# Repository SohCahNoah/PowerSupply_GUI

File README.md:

Junior Design 2 - Project
Group: EJ16
Project: DC-to-DC Power Supply with GUI interface

Steps to operate:
1. Connect the Arduino Uno to the host computer
2. Upload the firmware to the Arduino
3. Ensure that the correct pins are connected to the system for I2C communication (SDK, SDA, 5V VCC, GND)
4. Close any active Serial communications with the Arduino (such as in the Arduino IDE)
5. Run the Python Code

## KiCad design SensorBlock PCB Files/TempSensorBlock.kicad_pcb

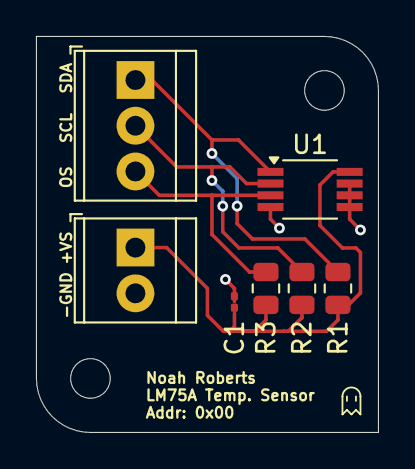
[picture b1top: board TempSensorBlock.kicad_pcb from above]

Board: 2 copper layers, 19.0 x 22.0 mm, 9 parts (0 on the bottom side), 5 nets.

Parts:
C1: 100nF; C_0201_0603Metric
H1, H1#2: MountingHole; MountingHole_2.2mm_M2
J1: Source Input (Screw); TerminalBlock_TE_282834-2_1x02_P2.54mm_Horizontal
J2: Microcontroller Terminal (Screw); TerminalBlock_TE_282834-3_1x03_P2.54mm_Horizontal
R1, R2, R3: 10k; R_0805_2012Metric
U1: LM75B; VSSOP-8_3.0x3.0mm_P0.65mm

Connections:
/+VS: C1.1, J1.1, R1.1, R2.1, R3.1, U1.8 (+Vs)
/OS: J2.3, R3.2, U1.3 (O.S.)
/SCL: J2.2, R2.2, U1.2 (SCL)
/SDA: J2.1, R1.2, U1.1 (SDA)
GND: C1.2, J1.2, U1.4 (GND), U1.5 (A2), U1.6 (A1), U1.7 (A0)

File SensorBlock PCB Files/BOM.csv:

"Reference","Value","Datasheet","Footprint","Qty","DNP","Supplier"
"H1,H2,H3,H4","MountingHole","~","MountingHole:MountingHole_2.2mm_M2","4","","(N/A)"
"R1,R2,R3","10k","~","Resistor_SMD:R_0805_2012Metric","3","","https://eecs.engineering.oregonstate.edu/education/tekbotSui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"
"C1","100nF","~","Capacitor_SMD:C_0201_0603Metric","1","","https://eecs.engineering.oregonstate.edu/education/tekbotSui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"
"U1","LM75B","http://www.ti.com/lit/ds/symlink/lm75b.pdf","Package_SO:VSSOP-8_3.0x3.0mm_P0.65mm","1","","https://eecs.engineering.oregonstate.edu/education/tekbotSui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"
"J1","Source Input (Screw)","~","TerminalBlock_TE-Connectivity:TerminalBlock_TE_282834-2_1x02_P2.54mm_Horizontal","1","","https://www.digikey.com/en/products/detail/te-connectivity-a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"
"J2","Microcontroller Terminal (Screw)","~","TerminalBlock_TE-Connectivity:TerminalBlock_TE_282834-3_1x03_P2.54mm_Horizontal","1","","https://www.digikey.com/en/products/detail/te-connectivity-a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"

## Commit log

2024-05-08 Version 1 of GUI
2024-05-08 Created EXE to run program
2024-05-08 Added Icon File
2024-05-08 Adjusted Icon Code to handle errors
2024-05-08 Updated EXE dependencies
2024-05-09 PCB files and Arduino code added to repo
2024-05-09 Updated to find Arduino port dynamically; updated to handle error if no device is found
2024-05-09 Updated line comments and added info header
2024-05-09 Fixed error with warning temp changes not affecting the color of the ambient temp
2024-05-09 Updated to include LCD code
2024-05-09 Updated header information
2024-05-12 Updated header
2024-05-14 Video Demo for Block 2
2024-05-15 Temp OS now updates if the user hits enter within the Entry Field
2024-05-15 Added todo bugfix item
2024-05-22 Arduino code updated to handle LCD screen
2024-05-24 Final Version - GUI Python File
2024-05-24 Rename gui_test_v2.py to PowerSupply_GUI.py
2024-06-02 Added documentation
